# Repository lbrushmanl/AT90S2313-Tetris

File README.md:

# AT90S2313-Tetris

To build ensure you have AVR GCC installed should be able to then build with
make all

To fash you need to have AVR Dude installed you can then flash/build with
make flash

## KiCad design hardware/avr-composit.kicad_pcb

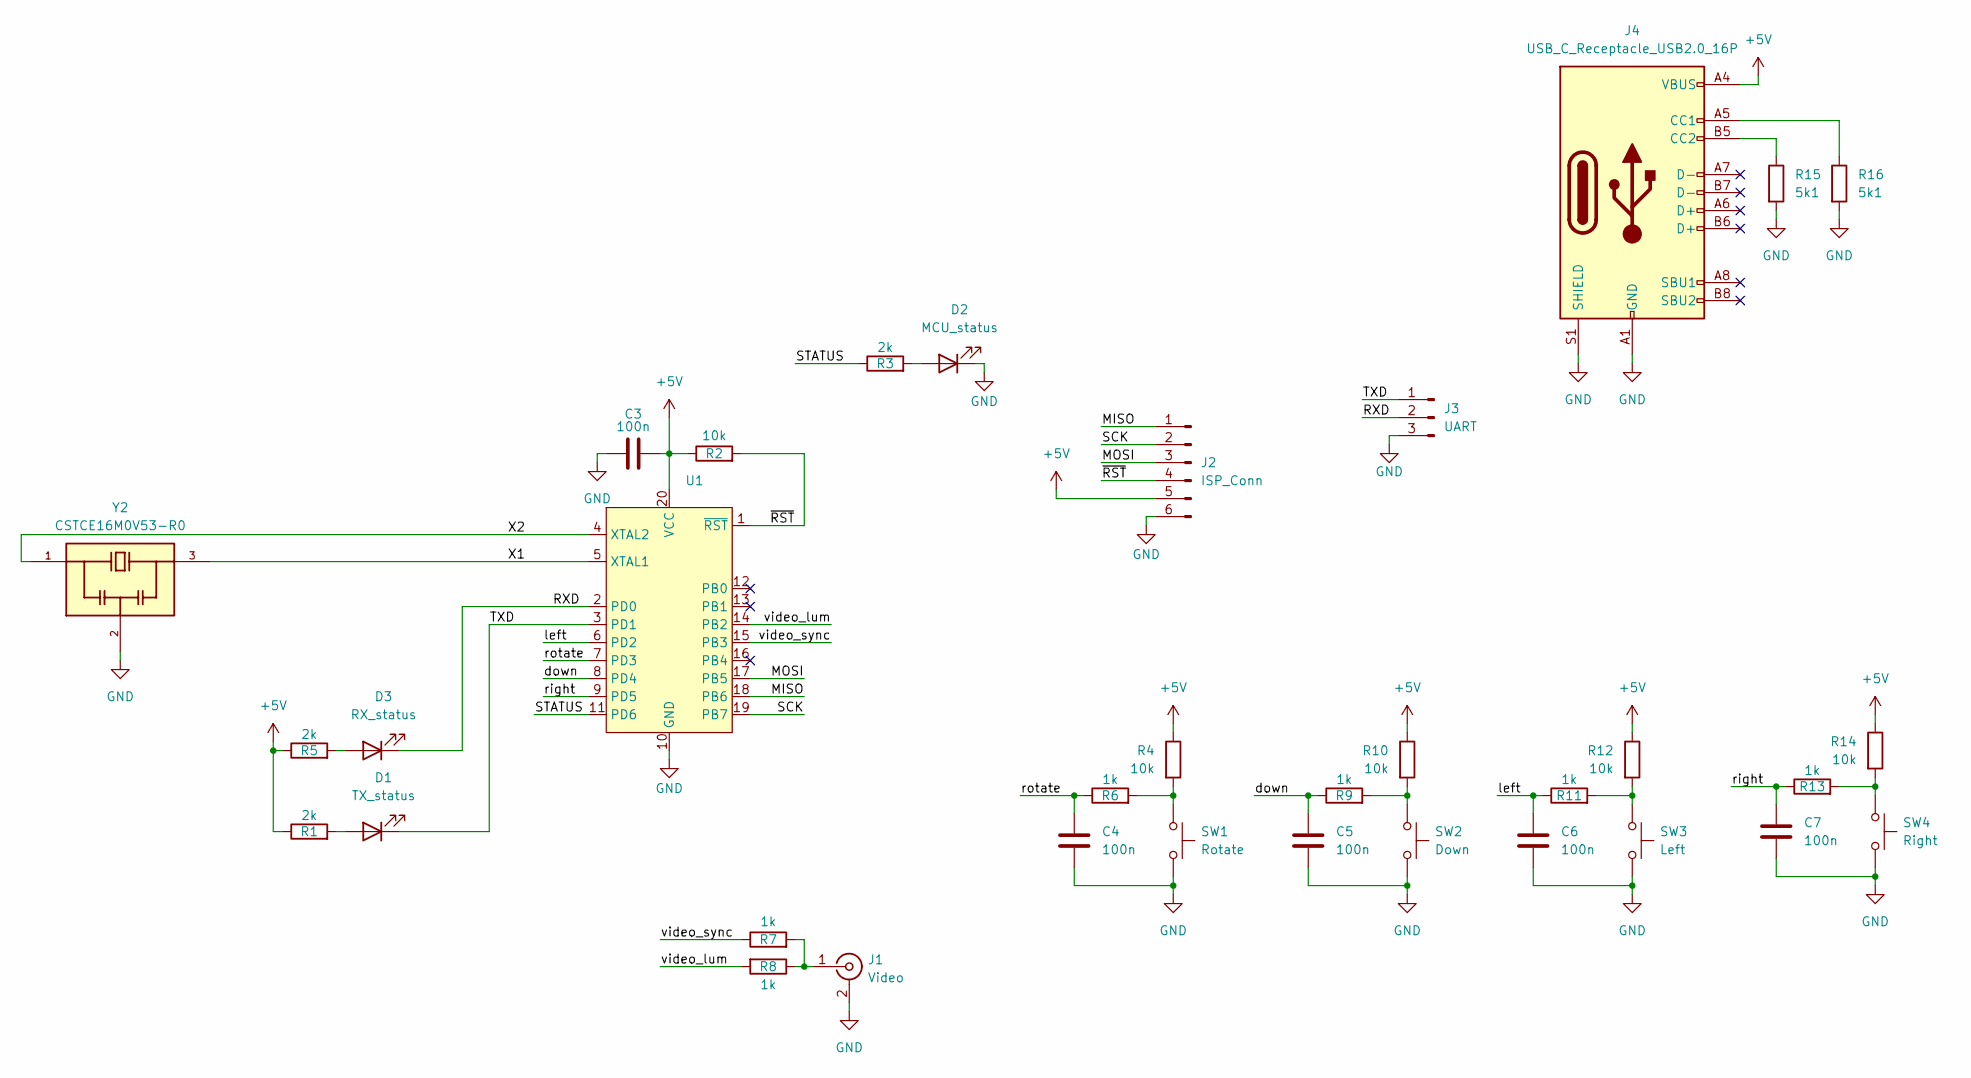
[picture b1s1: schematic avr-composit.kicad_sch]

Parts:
C3: 100n; C_0603_1608Metric_Pad1.08x0.95mm_HandSolder
C4, C5, C6, C7: 100n; C_0603_1608Metric
D1: TX_status; LED_0603_1608Metric
D2: MCU_status; LED_0603_1608Metric
D3: RX_status; LED_0603_1608Metric
J1: Video; CUI_RCJ-013
J2: ISP_Conn; PinHeader_2x03_P2.54mm_Vertical
J3: UART; PinHeader_1x03_P2.54mm_Vertical
J4: USB_C_Receptacle_USB2.0_16P; USB_C_Receptacle_G-Switch_GT-USB-7010ASV
R1, R3, R5: 2k; R_0603_1608Metric_Pad0.98x0.95mm_HandSolder
R2: 10k; R_0603_1608Metric_Pad0.98x0.95mm_HandSolder
R4, R10, R12, R14: 10k; R_0603_1608Metric
R6, R7, R8, R9, R11, R13: 1k; R_0603_1608Metric
R15, R16: 5k1; R_0603_1608Metric
SW1: Rotate; SW_PUSH_6mm
SW2: Down; SW_PUSH_6mm
SW3: Left; SW_PUSH_6mm
SW4: Right; SW_PUSH_6mm
U1: SOIC-20W_7.5x12.8mm_P1.27mm
Y2: CSTCE16M0V53-R0; OSC_CSTCE16M0V53-R0; PARTREV 10/24/2022

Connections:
+5V: C3.2, J2.5, J4.A4 (VBUS), J4.A9 (VBUS), J4.B4 (VBUS), J4.B9 (VBUS), R1.1, R2.1, R4.1, R5.1, R10.1, R12.1, R14.1, U1.20 (VCC)
/MISO: J2.1, U1.18 (PB6)
/MOSI: J2.3, U1.17 (PB5)
/RXD: D3.1 (K), J3.2, U1.2 (PD0)
/SCK: J2.2, U1.19 (PB7)
/STATUS: R3.1, U1.11 (PD6)
/TXD: D1.1 (K), J3.1, U1.3 (PD1)
/X1: U1.5 (XTAL1), Y2.3
/X2: U1.4 (XTAL2), Y2.1
/down: C5.1, R9.1, U1.8 (PD4)
/left: C6.1, R11.1, U1.6 (PD2)
/right: C7.1, R13.1, U1.9 (PD5)
/rotate: C4.1, R6.1, U1.7 (PD3)
/video_lum: R8.2, U1.14 (PB2)
/video_sync: R7.1, U1.15 (PB3)
/~RST: J2.4, R2.2, U1.1 (~RST)
GND: C3.1, C4.2, C5.2, C6.2, C7.2, D2.1 (K), J1.2 (Ext), J2.6, J3.3, J4.A1 (GND), J4.A12 (GND), J4.B1 (GND), J4.B12 (GND), J4.S1 (SHIELD), R15.2, R16.2, SW1.2, SW2.2, SW3.2, SW4.2, U1.10 (GND), Y2.2
unnamed: D1.2 (A), R1.2
unnamed: D2.2 (A), R3.2
unnamed: D3.2 (A), R5.2
unnamed: J1.1 (In), R7.2, R8.1
unnamed: J4.A5 (CC1), R16.1
unnamed: J4.B5 (CC2), R15.1
unnamed: R4.2, R6.2, SW1.1
unnamed: R9.2, R10.2, SW2.1
unnamed: R11.2, R12.2, SW3.1
unnamed: R13.2, R14.2, SW4.1

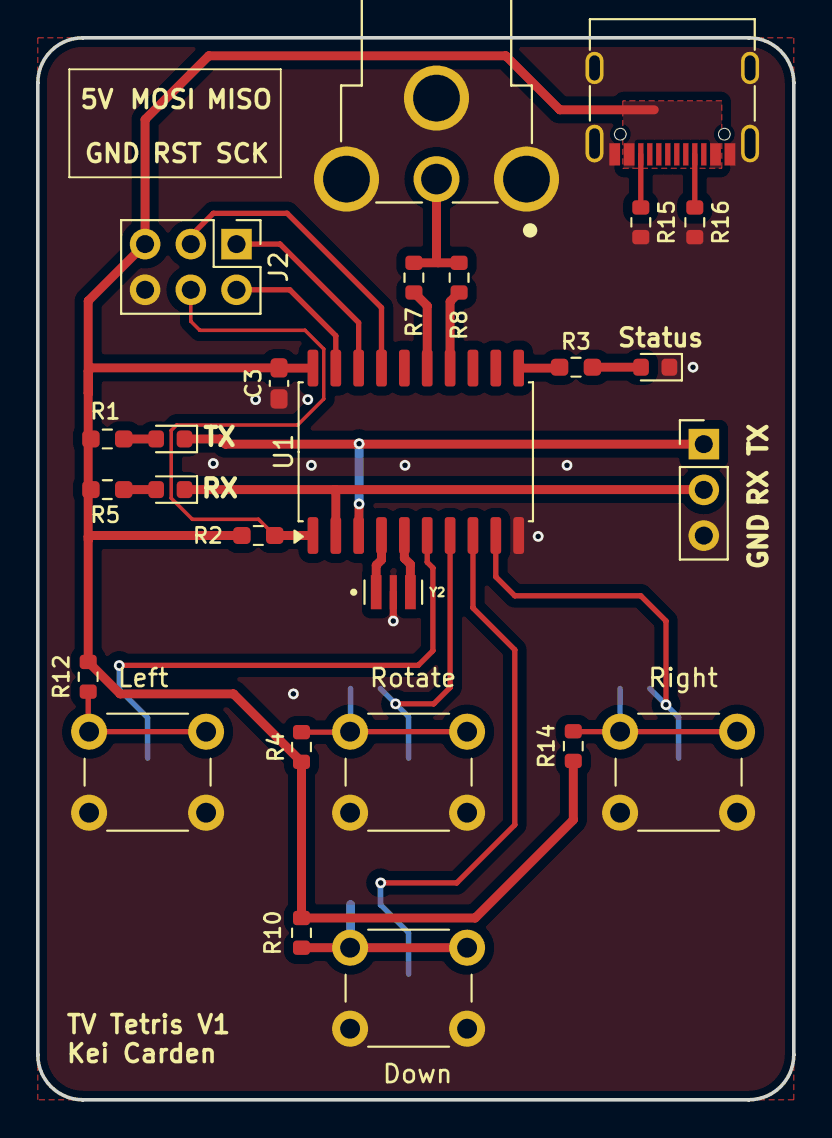
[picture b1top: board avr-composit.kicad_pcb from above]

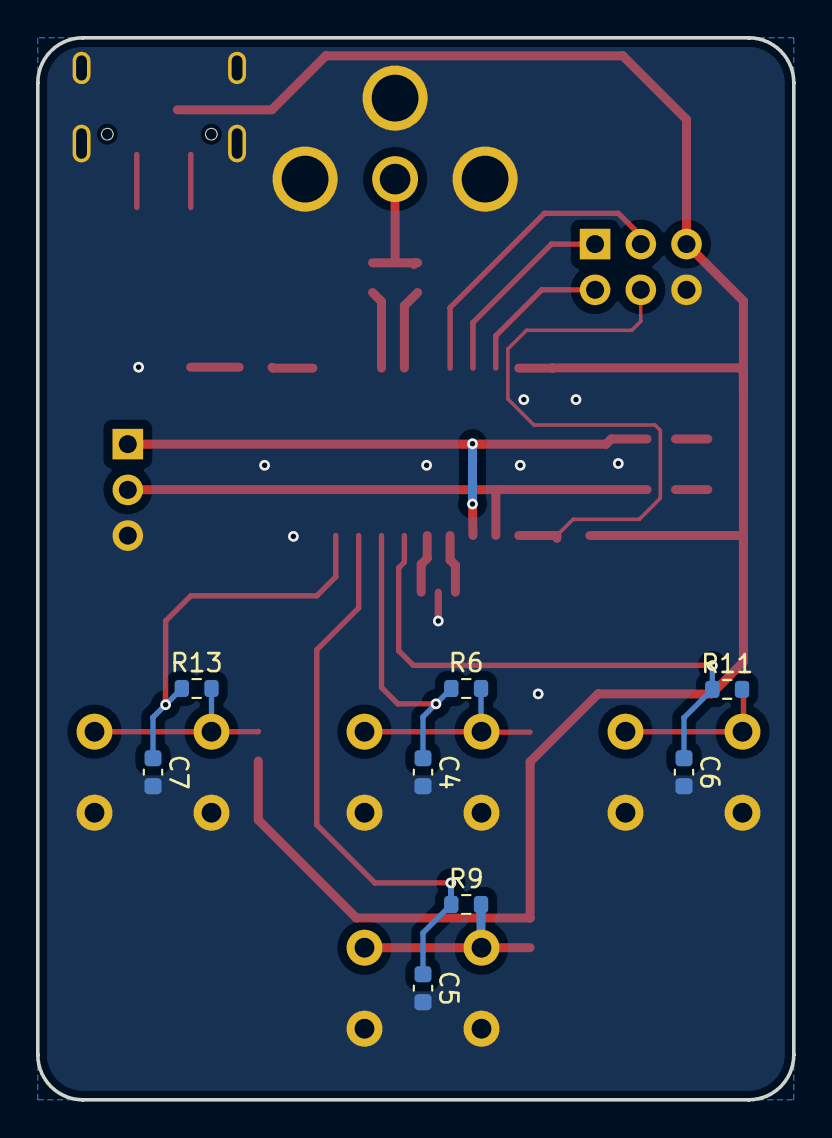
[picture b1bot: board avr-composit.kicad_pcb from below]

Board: 2 copper layers, 42.0 x 59.0 mm, 34 parts (8 on the bottom side), 27 nets.

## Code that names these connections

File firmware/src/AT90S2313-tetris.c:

#include <stdint.h>
#include <stdbool.h>

#include <avr/io.h>
#include <avr/interrupt.h>
#include <avr/pgmspace.h>
#include <util/delay.h>

#include "utils.h"
#include "tetromino_definitions.h"


#define LEFT_BUTTON PD2
#define ROTATE_BUTTON PD3
#define DOWN_BUTTON PD4
#define RIGHT_BUTTON PD5
#define BUTTONS PIND

#define LEFT_BUTTON_STATE()   (!READ_PIN(BUTTONS, LEFT_BUTTON))
#define RIGHT_BUTTON_STATE()  (!READ_PIN(BUTTONS, RIGHT_BUTTON))
#define DOWN_BUTTON_STATE()   (!READ_PIN(BUTTONS, DOWN_BUTTON))
#define ROTATE_BUTTON_STATE() (!READ_PIN(BUTTONS, ROTATE_BUTTON))

#define VIDEO_SYNC_PIN _BV(PB3) // 1k 
#define VIDEO_DATA_PIN _BV(PB2) // 470R

#define WIDTH_PIXELS             (10)
#define PIXEL_HIGHT_IN_LINES     (12U)
#define LINES_IN_FRAME           (312)
#define HIGHT_OF_GAME_AREA       (21)
#define HIGHT_OF_PLAYABLE_AREA   (21)

#define LOOP_COUNTER      (UBRR)
#define sub_pixel_counter (TCNT0)
#define pixel_line_number (EEDR)

#define FRAMES_BEFORE_GAME_LOGIC            (5U)
#define GAME_EXICUTION_CYCLES_TO_DROP_TETRO (3U)


typedef struct
{
    tetros_e tetro;
    uint8_t rotation;
    int8_t x;
    int8_t y;
} tetromino_t;


typedef enum
{
    CLEAR = 0,
    DRAW = 1,
    COLLISION = 2
} command_e;


static tetromino_t block = {4, 0, 7, HIGHT_OF_PLAYABLE_AREA};
static tetromino_t next_tetro = {0, 3, 0, 10};

static volatile uint16_t screen_data[HIGHT_OF_GAME_AREA] =
{
    0b111111111111000,
    0b100000000001000,
    0b100000000001000,
    0b100000000001000,
    0b100000000001000,
    0b100000000001000,
    0b100000000001000,
    0b100000000001000,
    0b100000000001000,
    0b100000000001000,
    0b100000000001000,
    0b100000000001000,
    0b100000000001000,
    0b100000000001000,
    0b100000000001000,
    0b100000000001000,
    0b100000000001000,
    0b100000000001000,
    0b100000000001000,
    0b100000000001000,
    0b100000000001000,
};

static volatile uint8_t wait = 0;
static uint8_t score = 0;


#pragma GCC push_options
#pragma GCC optimize ("-O1")
ISR (TIMER1_COMP1_vect)
{
    static uint16_t line_number = 0;
    // static uint8_t sub_pixel_counter = 0;
    // static uint8_t pixel_line_number = 0;

    SET_OUTPUT_LOW(PORTB, VIDEO_SYNC_PIN);    

    if (line_number > 2)
    {
        __builtin_avr_delay_cycles(65); // Sync 4.7us
        SET_OUTPUT_HIGH(PORTB, VIDEO_SYNC_PIN);

        if (line_number > 22 && line_number < 309) // Draw to screen
        {
            _delay_us(8); // Front porch

            if (pixel_line_number > 20)
            {
                pixel_line_number = 20;
            }
            
            
            uint16_t tmp_line_data = screen_data[pixel_line_number];

            // Draw pixels in line
            while (tmp_line_data)
            {
                if (tmp_line_data & 0x1)
                {
                    SET_OUTPUT_HIGH(PORTB, VIDEO_DATA_PIN);
                }
                else
                {
                    SET_OUTPUT_LOW(PORTB, VIDEO_DATA_PIN);
                }

                __builtin_avr_delay_cycles(30); // Sync 4.7us Pixel width
                tmp_line_data >>= 1;
            }

            SET_OUTPUT_LOW(PORTB, VIDEO_DATA_PIN);

            if (sub_pixel_counter < PIXEL_HIGHT_IN_LINES)
            {
                sub_pixel_counter++;
            }
            else
            {
                sub_pixel_counter = 0;
                pixel_line_number++;
            }
        }
    }

    if (line_number < LINES_IN_FRAME)
    {
        line_number++;
        return;
    } 

    line_number = 0;
    pixel_line_number = 0;
    wait++;
}
#pragma GCC pop_options


static inline void init_line_clock(void)
{
    sub_pixel_counter = 0;
    pixel_line_number = 0;
    CONFIG_PIN(DDRB, VIDEO_SYNC_PIN | VIDEO_DATA_PIN);
    SET_OUTPUT_HIGH(PORTB, VIDEO_SYNC_PIN);
    SET_OUTPUT_LOW(PORTB, VIDEO_DATA_PIN);

    TCCR1B |= _BV(CS10); // Set CLK divider to 1
    TCCR1B |= _BV(CTC1); // Reset timer after valid compear
    TIMSK  |= _BV(OCIE1A); // Enable timer interupt

    // 15.625Khz
    // Have to tune to get the correct freq
    OCR1AH = 4;
    OCR1AL = 3;

    sei();
}


static void game_over(void)
{
    for (LOOP_COUNTER = 0; LOOP_COUNTER < HIGHT_OF_GAME_AREA; LOOP_COUNTER++)
    {
        screen_data[LOOP_COUNTER] = 0;
    }

    uint16_t number = pgm_read_word(&numbers[score % 10]);

    for (LOOP_COUNTER = 0; LOOP_COUNTER < 5; LOOP_COUNTER++)
    {
        screen_data[10 + LOOP_COUNTER] = ((number >> (LOOP_COUNTER * 3)) & 0b111) << 10;
    }

    score /= 10;

    number = pgm_read_word(&numbers[score % 10]);

    for (LOOP_COUNTER = 0; LOOP_COUNTER < 5; LOOP_COUNTER++)
    {
        screen_data[10 + LOOP_COUNTER] = ((number >> (LOOP_COUNTER * 3)) & 0b111) << 4;
    }

    while (true);
}


static bool game_logic(command_e command, tetromino_t *tetro)
{
    uint16_t line = pgm_read_word(&tetros[tetro->tetro][tetro->rotation]);
    uint8_t mask = 0b111;
    uint8_t bits = 3;

    if (tetro->tetro == TETRO_STRAIGHT)
    {
        mask = 0b1111;
        bits = 4;
    }

    for (LOOP_COUNTER = 0; LOOP_COUNTER < bits; LOOP_COUNTER++)
    {
        if (tetro->y + LOOP_COUNTER > HIGHT_OF_PLAYABLE_AREA)
        {
            return false;
        }

        uint16_t row = ((line >> (LOOP_COUNTER * bits)) & mask) << tetro->x;

        switch (command)
        {
        case DRAW:
            screen_data[tetro->y + LOOP_COUNTER] |= row;
            break;

        case COLLISION:
            if (screen_data[tetro->y + LOOP_COUNTER] & row)
            {
                if (tetro->y + LOOP_COUNTER >= HIGHT_OF_PLAYABLE_AREA)
                {
                    game_over();
                }
                
                return true;
            }

            break;
        
        case CLEAR:
            screen_data[tetro->y + LOOP_COUNTER] &= ~row;
            break;
        }
    }

    return false;
}


static inline bool poll_direction_buttons(void)
{
    static uint8_t time_to_move_down = 0;

    if (time_to_move_down == 3)
    {
        time_to_move_down = 0;
    } else
    {
        time_to_move_down++;
    }

    if (ROTATE_BUTTON_STATE())
    {
        block.rotation++;
        block.rotation %= 4;
        block.rotation -= game_logic(COLLISION, &block);
        if (block.rotation == 255)
        {
            block.rotation = 3;
        }
    }
    
    if (LEFT_BUTTON_STATE())
    {
        block.x++;
        block.x -= game_logic(COLLISION, &block);
    } 
    
    if (RIGHT_BUTTON_STATE())
    {
        block.x--;
        block.x += game_logic(COLLISION, &block);
    }
    
    if (DOWN_BUTTON_STATE() || (time_to_move_down == GAME_EXICUTION_CYCLES_TO_DROP_TETRO))
    {
        block.y--;
        bool collision = game_logic(COLLISION, &block);
        block.y += collision;
        return collision;
    }

    return false;
}

// https://www.analog.com/en/resources/design-notes/random-number-generation-using-lfsr.html
// XOR-based feedback shift register
static uint8_t seed = 0xB8; // Initial seed (can be any non-zero value)

static tetros_e random(void)
{
    // Linear Feedback Shift Register (LFSR)
    seed ^= (seed << 1);
    seed ^= (seed >> 1);
    seed ^= (seed << 5);

    return (seed & 0xFF) % 6; // Generate numbers in range [0, 5]
}

static void update_next_tetro(void)
{
    game_logic(CLEAR, &next_tetro);
    next_tetro.tetro = random();
    game_logic(DRAW, &next_tetro);
}


static inline bool check_full_line(void)
{
    for (LOOP_COUNTER = 1; LOOP_COUNTER < HIGHT_OF_PLAYABLE_AREA; LOOP_COUNTER++)
    {
        if ((screen_data[LOOP_COUNTER] & 0b11111111110000) == 0b11111111110000)
        {
            for (; LOOP_COUNTER < HIGHT_OF_PLAYABLE_AREA; LOOP_COUNTER++)
            {
                screen_data[LOOP_COUNTER] = screen_data[LOOP_COUNTER + 1]; // TODO: Only copy game area
            }

            score++;

            return true;
        }                
    }

    return false;
}


int main(void)
{
    init_line_clock();

    CONFIG_PIN(DDRD, _BV(PD6));

    update_next_tetro();

    SET_OUTPUT_LOW(PORTD, _BV(PD6));

    while (true)
    {
        if (wait == FRAMES_BEFORE_GAME_LOGIC)
        {
            bool collision = false;

            if (!check_full_line())
            {
                // Clear the tetro from the screen buffer
                game_logic(CLEAR, &block);

                // Get new direction
                collision = poll_direction_buttons();  
            }          

            // Draw tetro to screen buffer
            game_logic(DRAW, &block);

            if (collision)
            {
                block.x = 7;
                block.y = HIGHT_OF_PLAYABLE_AREA;
                block.rotation = 0;
                block.tetro = next_tetro.tetro;
                update_next_tetro();
            }
            
            wait = 0;
        }
    }
    
    return 0;
}

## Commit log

2025-05-04 Fist commit. Adding mostly complete tetris game running on the AT90S2313
    The game was designed around the board in this repo and uses composit to the display the game to a TV
